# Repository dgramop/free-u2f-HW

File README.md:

# free-u2f-HW
Hardware for the "free-u2f" u2f security key based on the CH552T, a cheap 8051-based microcontroller with a USB interface

## Pin compatibility
The CH552T and the CH554T should be mostly pin-compatible.

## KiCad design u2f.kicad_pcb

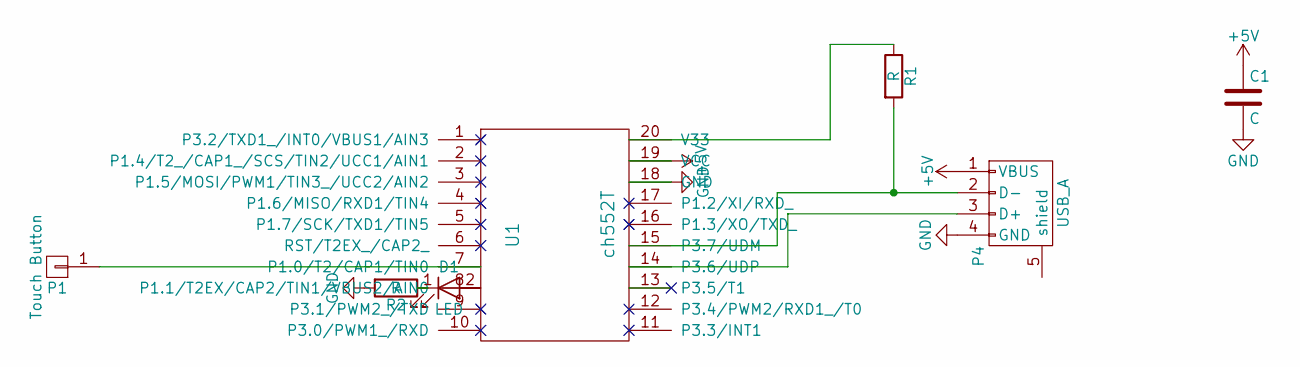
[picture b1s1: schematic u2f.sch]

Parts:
C1: C; C_0805_HandSoldering
D1: LED; LED_0805
P1: Touch Button; EdgeTouch
P4: USB_A; USBEdge
R1, R2: R; R_0805_HandSoldering
U1: ch552T; TSSOP-20_4.4x6.5mm_Pitch0.65mm

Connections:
+5V: C1.1, P4.1 (VBUS), U1.19 (VCC)
GND: C1.2, P4.4 (GND), R2.2, U1.18 (GND)
unnamed: D1.1 (K), R2.1
unnamed: D1.2 (A), U1.8 (P1.1/T2EX/CAP2/TIN1/VBUS2/AIN0)
unnamed: P1.1, U1.7 (P1.0/T2/CAP1/TIN0)
unnamed: P4.2 (D-), R1.2, U1.15 (P3.7/UDM)
unnamed: P4.3 (D+), U1.14 (P3.6/UDP)
unnamed: R1.1, U1.20 (V33)

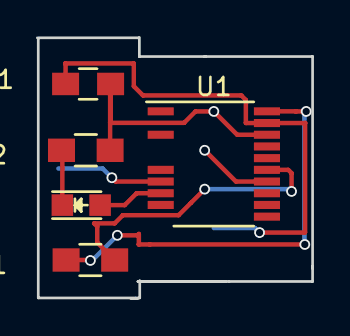
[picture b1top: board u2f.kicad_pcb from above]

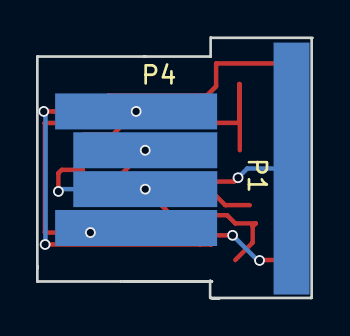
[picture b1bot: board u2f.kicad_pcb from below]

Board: 2 copper layers, 15.3 x 14.5 mm, 7 parts (2 on the bottom side), 8 nets.

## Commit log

2019-06-05 lets go
2019-06-06 added some new footprints and stuff.
    I'm having issues connecting everything up while keeping my optimal dimensions.
    Options are to
    - switch around some the GPIO pins (for LED) to avoid having traces run accross components
    - Remove resistor and offload it to only when I'm programming (or directly wire D- and VCC to a "resistor", which will only be there during programmin)
    - Remove programming pins and pre-program chip before putting it on the board (then I'd have to design a programmer PCB)
    - (nucelar option) add an extra layer (basically two because I've never heard of a 3-layer PCB)
2019-06-07 checking in code for tonight. It's def. not perfect I've removed pins from the IC footprint. The fact that this is a bad practice is not lost on me
    I just need to re-route power and GND so that the USB actually fits the correct dimensions.
    Once that is done I will work on edge cuts and look at some boardhouses to see who is willing to make this
2019-06-07 made the traces a little better. I think I should rotate one of the resistors to avoid some of that wire jumping-around, but I guess it'll work
    If it becomes a problem later I'll fix it.
    I'll place the order for these boards after I get started working on the software. I want to be ready in the unlikely case that I need more pins or sometihng. Otherwise, I think I'll just internall p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
    The first order will just be a test batch for functionality, then I'll actually clean up my design so it looks less like absolute shit and then do another prototype run followed by a bulk run
